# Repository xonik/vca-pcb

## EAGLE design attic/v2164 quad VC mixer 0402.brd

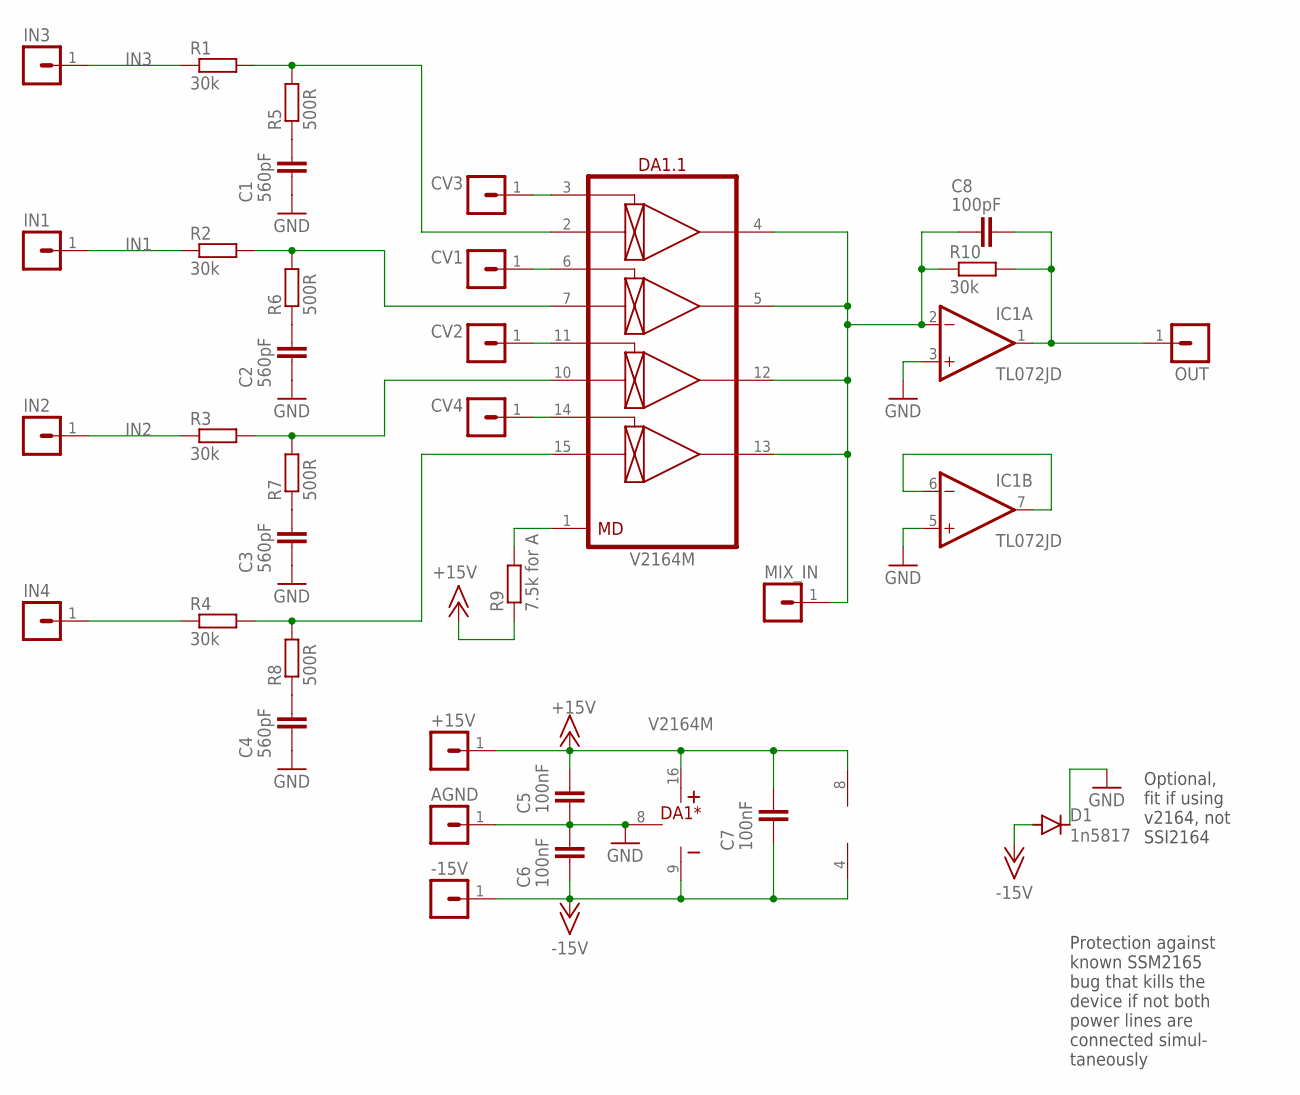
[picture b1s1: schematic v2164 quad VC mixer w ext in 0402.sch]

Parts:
+15V: MA01-1JN; MA01N-1J
-15V: MA01-1JN; MA01N-1J
AGND: MA01-1JN; MA01N-1J
C1, C2, C3, C4: 560pF; C0603
C5, C6, C7: 100nF; C0402
C8: 100pF; C0402
CV1, CV2, CV3, CV4: MA01-1JN; MA01N-1J
D1: 1n5817; SOD323-R
DA1: V2164M; SO-16
IC1: TL072JD; SO08J
IN1, IN2, IN3, IN4: MA01-1JN; MA01N-1J
MIX_IN: MA01-1JN; MA01N-1J
OUT: MA01-1JN; MA01N-1J
R1, R2, R3, R4, R10: 30k; R0402
R5, R6, R7, R8: 500R; R0402
R9: 7.5k for A; R0402

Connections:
+15V: +15V.1, C5.2, C7.2, DA1.16 (V+), IC1.8 (V+), R9.1
-15V: -15V.1, C6.1, C7.1, D1.A, DA1.9 (V-), IC1.4 (V-); also elsewhere on the board
CV1: CV1.1, DA1.6 (CV2)
CV2: CV2.1, DA1.11 (CV3)
CV4: CV4.1, DA1.14 (CV4)
CV5: CV3.1, DA1.3 (CV1)
GND: AGND.1, C1.1, C2.1, C3.1, C4.1, C5.1, C6.2, D1.C, DA1.8 (GND), IC1.3 (+IN), IC1.5 (+IN); also elsewhere on the board
IN1: IN1.1, R2.1
IN2: IN2.1, R3.1
IN3: IN3.1, R1.1
IN4: IN4.1, R4.1
unnamed: IC1.6 (-IN), IC1.7 (OUT)
unnamed: DA1.1 (MD), R9.2
unnamed: C8.1, DA1.4 (OUT1), DA1.5 (OUT2), DA1.12 (OUT3), DA1.13 (OUT4), IC1.2 (-IN), MIX_IN.1, R10.1
unnamed: C1.2, R5.1
unnamed: C2.2, R6.1
unnamed: C3.2, R7.1
unnamed: C4.2, R8.1
unnamed: DA1.2 (IN1), R1.2, R5.2
unnamed: DA1.7 (IN2), R2.2, R6.2
unnamed: DA1.10 (IN3), R3.2, R7.2
unnamed: DA1.15 (IN4), R4.2, R8.2
OUT: C8.2, IC1.1 (OUT), OUT.1, R10.2

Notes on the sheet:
Optional, fit if using v2164, not SSI2164
Protection against known SSM2165 bug that kills the device if not both power lines are connected simul- taneously

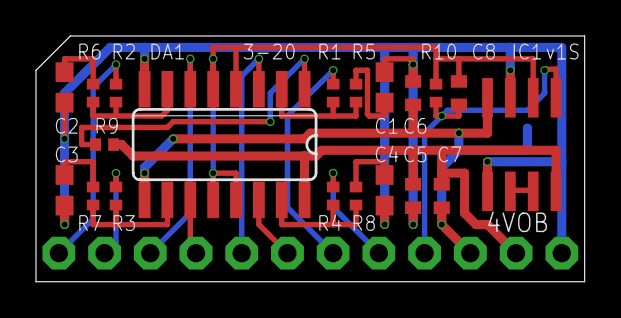
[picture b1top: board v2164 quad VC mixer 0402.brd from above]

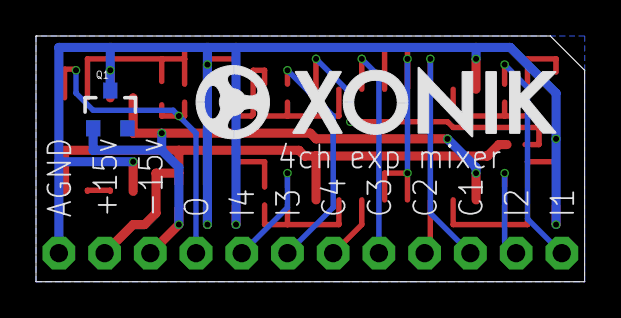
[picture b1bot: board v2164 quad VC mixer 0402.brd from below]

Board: 2 copper layers, 30.5 x 13.7 mm, 34 parts (2 on the bottom side), 23 nets.

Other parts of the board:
Q1: BA854SW; SOT23-3J
U$1: XONIK_LOGO_20

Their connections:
-15V: Q1.1; also elsewhere on the board
GND: Q1.3; also elsewhere on the board

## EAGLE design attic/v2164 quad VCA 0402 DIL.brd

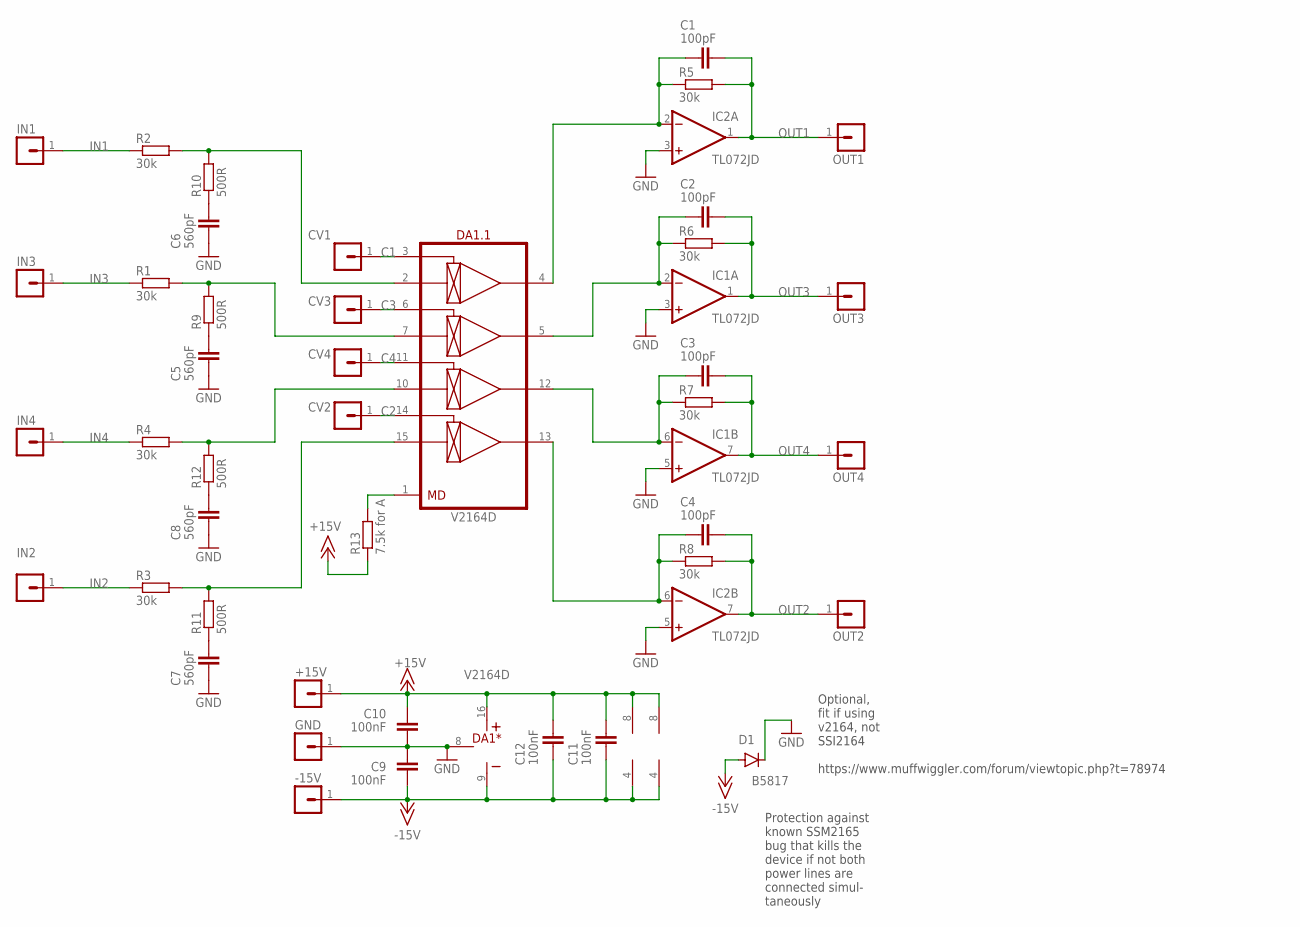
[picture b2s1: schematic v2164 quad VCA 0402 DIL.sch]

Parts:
+15V: MA01-1JP; SIP-PIN01-1J
-15V: MA01-1JP; SIP-PIN01-1J
C1, C2, C3, C4: 100pF; C0402
C5, C6, C7, C8: 560pF; C0603
C9, C10, C11, C12: 100nF; C0402
CV1, CV2, CV3, CV4: MA01-1JP; SIP-PIN01-1J
D1: B5817; SOD323-R
DA1: V2164D; DIP-16
GND: MA01-1JP; SIP-PIN01-1J
IC1, IC2: TL072JD; SO08J
IN1, IN2, IN3, IN4: MA01-1JP; SIP-PIN01-1J
OUT1, OUT2, OUT3, OUT4: MA01-1JP; SIP-PIN01-1J
R1, R2, R3, R4, R5, R6, R7, R8: 30k; R0402
R9, R10, R11, R12: 500R; R0402
R13: 7.5k for A; R0402

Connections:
+15V: +15V.1, C10.2, C11.2, C12.2, DA1.16 (V+), IC1.8 (V+), IC2.8 (V+), R13.1
-15V: -15V.1, C9.1, C11.1, C12.1, D1.A, DA1.9 (V-), IC1.4 (V-), IC2.4 (V-)
C1: CV1.1, DA1.3 (CV1)
C2: CV2.1, DA1.14 (CV4)
C3: CV3.1, DA1.6 (CV2)
C4: CV4.1, DA1.11 (CV3)
GND: C5.1, C6.1, C7.1, C8.1, C9.2, C10.1, D1.C, DA1.8 (GND), GND.1, IC1.3 (+IN), IC1.5 (+IN), IC2.3 (+IN), IC2.5 (+IN)
IN1: IN1.1, R2.1
IN2: IN2.1, R3.1
IN3: IN3.1, R1.1
IN4: IN4.1, R4.1
unnamed: C4.1, DA1.13 (OUT4), IC2.6 (-IN), R8.1
unnamed: DA1.1 (MD), R13.2
unnamed: C3.1, DA1.12 (OUT3), IC1.6 (-IN), R7.1
unnamed: C2.1, DA1.5 (OUT2), IC1.2 (-IN), R6.1
unnamed: C1.1, DA1.4 (OUT1), IC2.2 (-IN), R5.1
unnamed: C5.2, R9.1
unnamed: C6.2, R10.1
unnamed: C7.2, R11.1
unnamed: C8.2, R12.1
unnamed: DA1.7 (IN2), R1.2, R9.2
unnamed: DA1.2 (IN1), R2.2, R10.2
unnamed: DA1.15 (IN4), R3.2, R11.2
unnamed: DA1.10 (IN3), R4.2, R12.2
OUT1: C1.2, IC2.1 (OUT), OUT1.1, R5.2
OUT2: C4.2, IC2.7 (OUT), OUT2.1, R8.2
OUT3: C2.2, IC1.1 (OUT), OUT3.1, R6.2
OUT4: C3.2, IC1.7 (OUT), OUT4.1, R7.2

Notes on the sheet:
Optional, fit if using v2164, not SSI2164 https://www.muffwiggler.com/forum/viewtopic.php?t=78974
Protection against known SSM2165 bug that kills the device if not both power lines are connected simul- taneously

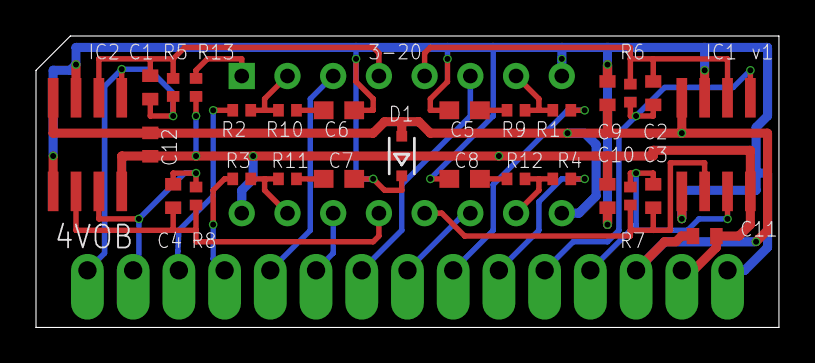
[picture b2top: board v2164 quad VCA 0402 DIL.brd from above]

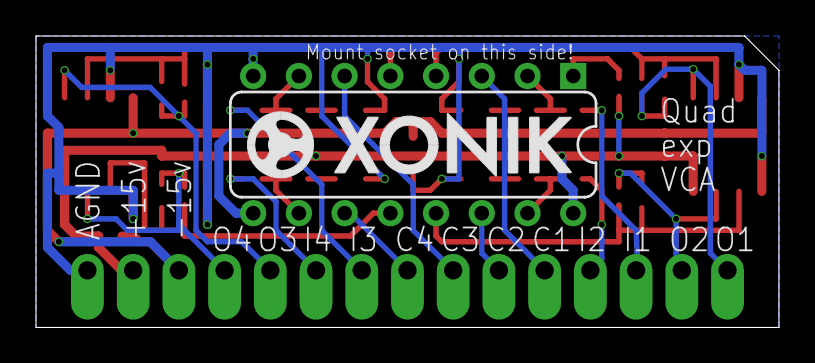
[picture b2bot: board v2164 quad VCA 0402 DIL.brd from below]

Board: 2 copper layers, 41.3 x 16.2 mm, 45 parts (2 on the bottom side), 28 nets.

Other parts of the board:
U$1: XONIK_LOGO_18

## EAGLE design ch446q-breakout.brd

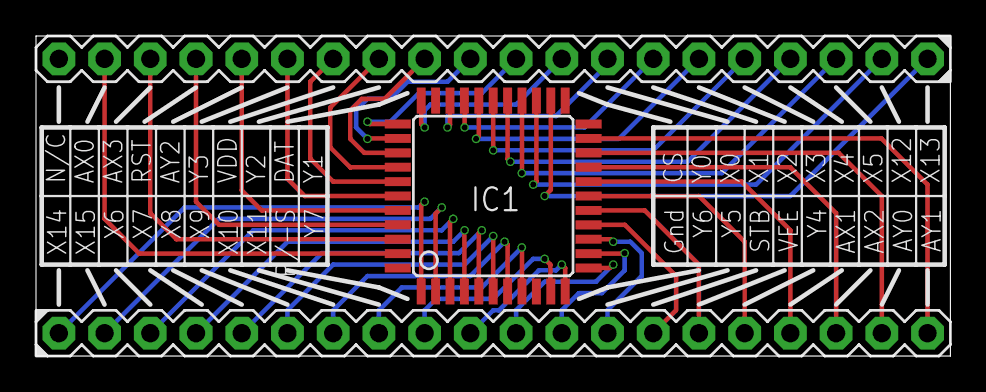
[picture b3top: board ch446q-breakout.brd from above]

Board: 2 copper layers, 50.8 x 17.8 mm, 3 parts (0 on the bottom side), 39 nets.

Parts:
IC1: CH446Q; LQFP-44-J
SV1, SV2: MA20-1J

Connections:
AX0: IC1.43, SV2.19
AX1: IC1.18, SV1.17
AX2: IC1.19, SV1.18
AX3: IC1.42, SV2.18
AY0: IC1.20, SV1.19
AY1: IC1.21, SV1.20
AY2: IC1.40, SV2.16
CS/CK: IC1.34, SV2.10
DAT: IC1.36, SV2.12
GND: IC1.12, SV1.11
P/-S: IC1.10, SV1.9
RST: IC1.41, SV2.17
STB: IC1.14, SV1.14
VDD: IC1.38, SV2.14
VEE: IC1.16, SV1.15
X0: IC1.31, SV2.8
X1: IC1.30, SV2.7
X2: IC1.29, SV2.6
X3: IC1.28, SV2.5
X4: IC1.27, SV2.4
X5: IC1.26, SV2.3
X6: IC1.3, SV1.3
X7: IC1.4, SV1.4
X8: IC1.5, SV1.5
X9: IC1.6, SV1.6
X10: IC1.7, SV1.7
X11: IC1.8, SV1.8
X12: IC1.25, SV2.2
X13: IC1.24, SV2.1
X14: IC1.1, SV1.1
X15: IC1.2, SV1.2
Y0: IC1.33, SV2.9
Y1: IC1.35, SV2.11
Y2: IC1.37, SV2.13
Y3: IC1.39, SV2.15
Y4: IC1.17, SV1.16
Y5: IC1.15, SV1.13
Y6: IC1.13, SV1.12
Y7: IC1.11, SV1.10
